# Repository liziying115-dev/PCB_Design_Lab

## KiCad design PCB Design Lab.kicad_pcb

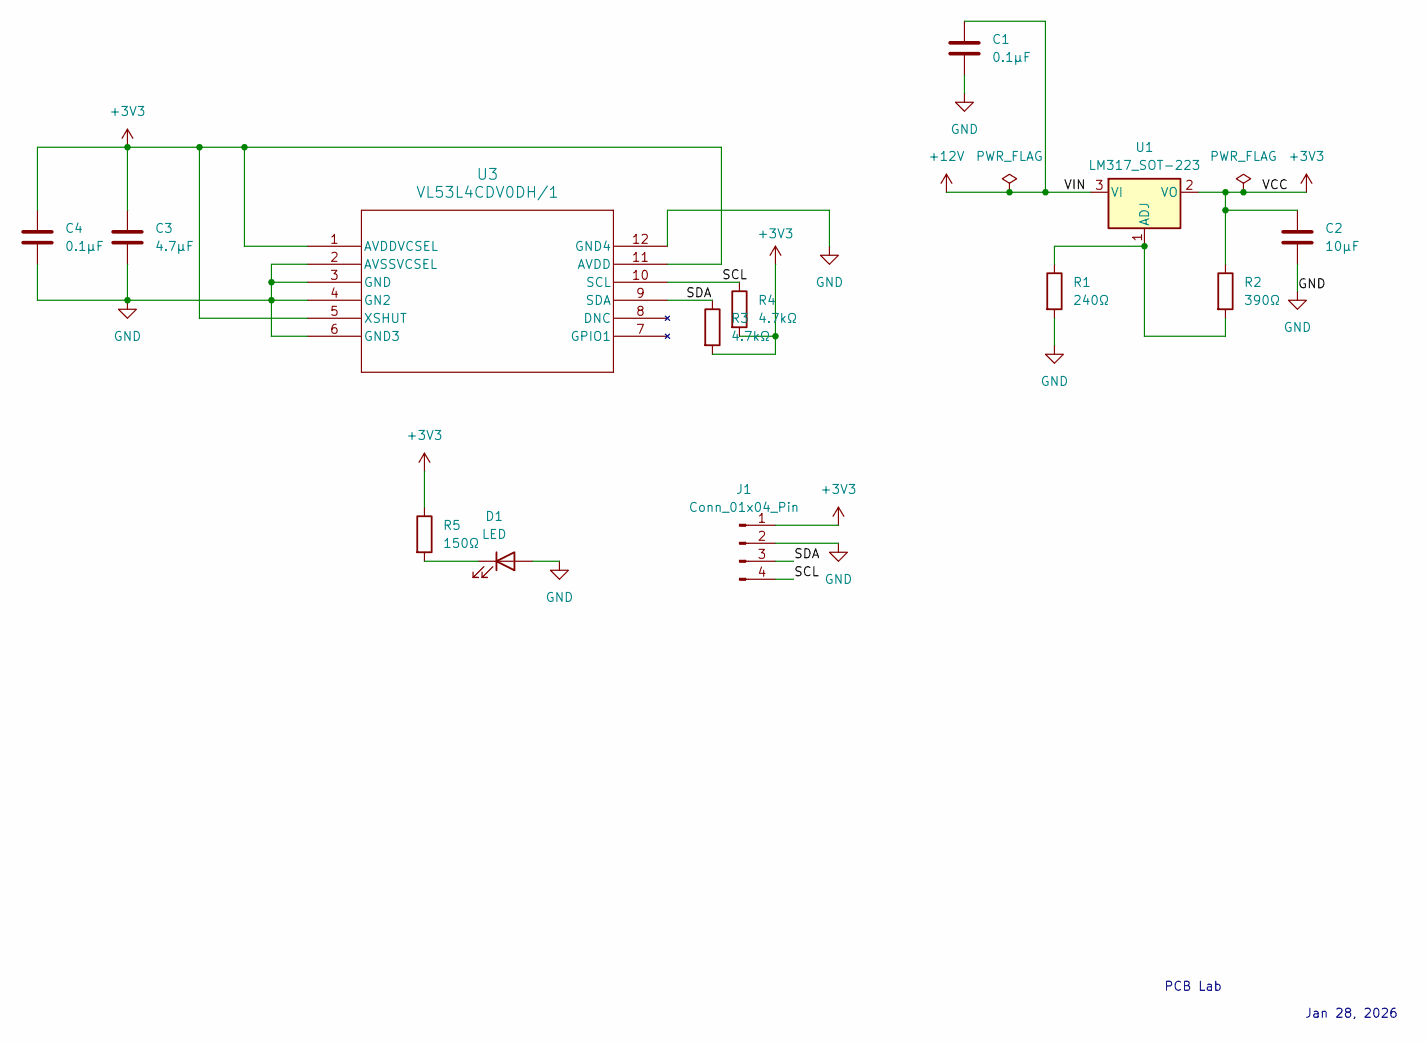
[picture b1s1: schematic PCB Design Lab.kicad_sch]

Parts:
C1, C4: 0.1µF; C_0805_2012Metric
C2: 10µF; C_0805_2012Metric
C3: 4.7µF; C_0805_2012Metric
D1: LED; LED_0805_2012Metric
J1: Conn_01x04_Pin; PinHeader_1x04_P2.54mm_Horizontal
R1: 240Ω; R_0805_2012Metric
R2: 390Ω; R_0805_2012Metric
R3, R4: 4.7kΩ; R_0805_2012Metric
R5: 150Ω; R_0805_2012Metric
U1: LM317_SOT-223; SOT-223-3_TabPin2
U3: VL53L4CDV0DH/1; LGA12_STM

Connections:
+3V3: C2.1, C3.1, C4.1, J1.1, R2.1, R3.2, R4.2, R5.1, U1.2 (VO), U3.1 (AVDDVCSEL), U3.5 (XSHUT), U3.11 (AVDD)
+12V: C1.1, U1.3 (VI)
/SCL: J1.4, R4.1, U3.10 (SCL)
/SDA: J1.3, R3.1, U3.9 (SDA)
GND: C1.2, C2.2, C3.2, C4.2, D1.2 (A), J1.2, R1.2, U3.2 (AVSSVCSEL), U3.3 (GND), U3.4 (GN2), U3.6 (GND3), U3.12 (GND4)
unnamed: D1.1 (K), R5.2
unnamed: R1.1, R2.2, U1.1 (ADJ)

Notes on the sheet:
PCB Lab
Jan 28, 2026

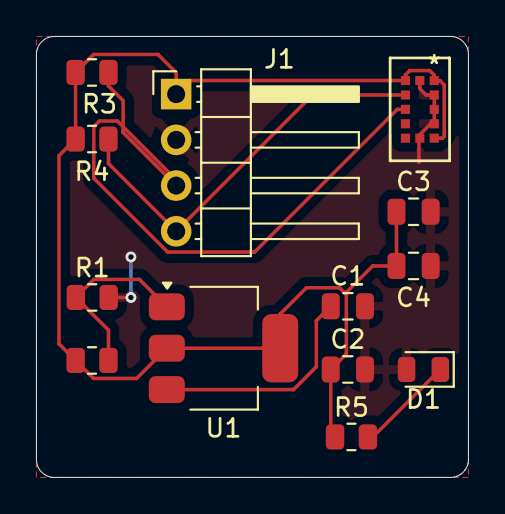
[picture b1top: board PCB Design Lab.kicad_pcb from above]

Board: 2 copper layers, 24.0 x 24.5 mm, 13 parts (0 on the bottom side), 7 nets.

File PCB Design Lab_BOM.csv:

"Id";"Designator";"Footprint";"Quantity";"Designation";"Supplier and ref";
1;"R4,R3";"R_0805_2012Metric";2;"4.7kΩ";;;
2;"J1";"PinHeader_1x04_P2.54mm_Horizontal";1;"Conn_01x04_Pin";;;
3;"C3";"C_0805_2012Metric";1;"4.7µF";;;
4;"C4,C1";"C_0805_2012Metric";2;"0.1µF";;;
5;"R1";"R_0805_2012Metric";1;"240Ω";;;
6;"R5";"R_0805_2012Metric";1;"150Ω";;;
7;"D1";"LED_0805_2012Metric";1;"LED";;;
8;"C2";"C_0805_2012Metric";1;"10µF";;;
9;"R2";"R_0805_2012Metric";1;"390Ω";;;
10;"U1";"SOT-223-3_TabPin2";1;"LM317_SOT-223";;;
11;"U3";"LGA12_STM";1;"VL53L4CDV0DH/1";;;

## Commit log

2026-01-30 rename bom
